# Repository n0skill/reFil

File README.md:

# reFil
A machine that makes filament suitable for 3D printers out of normally unrecycled plastic parts such as HDPE from bottle caps, failed prints etc.

# Folders
* schematics - All of the schematics made with KiCAD. Including the gerber files, kicad files (schematic, netlist, pcb, etc.)
* src - The source code running on the arduino nano (arduino/C/AVR ASM)
* mechanics - mechanical parts

# Material
The following material is needed for the whole project.

## Mechanical parts
The machine is made of lathed aluminium and brass.
All the plans will be available in the "mechanical" folder. Including 3D models, plans and specs

## Electrical parts
The controller board consists of an arduino nano and a custom board. Using a 24V power supply, a LM7805 regulator is used to drop down the voltage to a usable 5V signal to drive the logic. Since the drop is quite significant and the LM7805 is a simple linear regulator, a decent amount of heat will be produced. This can compromise the functionality of the circuit, so a heat sink has to be appended to it in order to better disipate the heat.

The board will be used to: 
1) display the current temperature
2) drive the motor
3) drive the heating element

### Temperature sensor
The temperature sensor consists of a PT1000 RTD as part of a voltage divider circuit. The conversion from voltage to temperature can be made by either: looking up a table, or using a formula.

Once the temperature is known, the arduino uses BCD encoding to controll the CD4543BE 7 segment display driver, which displays the temperature.

### Motor driver
The motor is a E192.24.246 Micromotors brushed DC thing. It has a 1:246 gearbox that allows it to move things with a high torque (at the expense of a lower rate of rotation. But we don't care about that)

It is using the 24V from the barrel jack and is toggled using a SRD-05VDC-SL-C relay from SONGLE industries.

### Heating element

The heating element is a simple nichrome wire that is also toggled with a relay on the 24V power line.

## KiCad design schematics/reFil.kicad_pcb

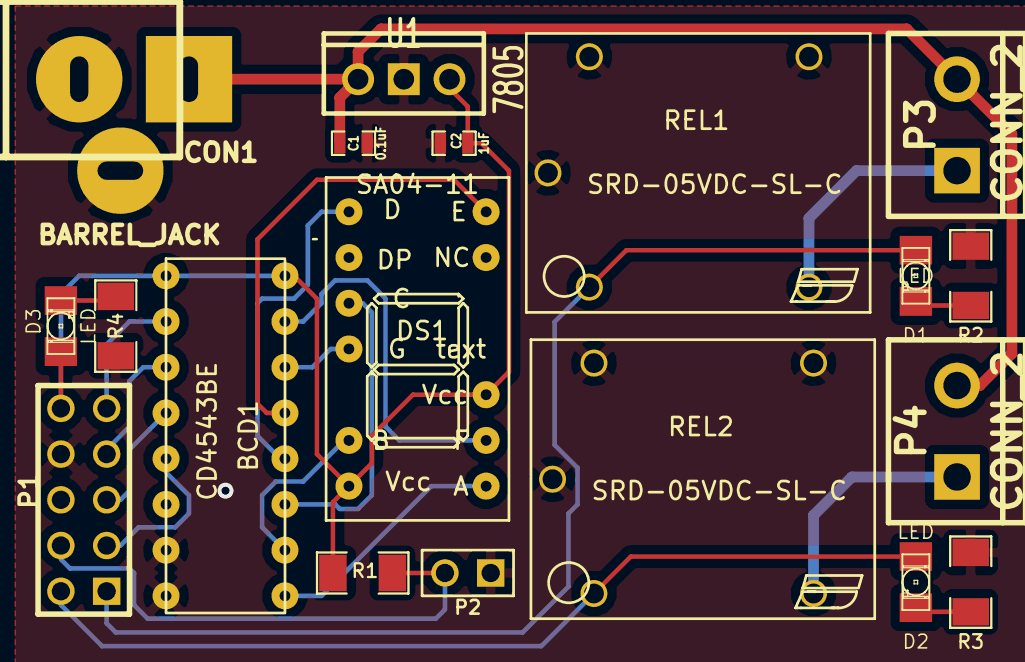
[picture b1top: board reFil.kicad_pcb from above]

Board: 2 copper layers, 19 parts (0 on the bottom side), 22 nets.

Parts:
BCD1: CD4543BE
C1: 0.1uF; SM0603_Capa
C2: 1uF; SM0603_Capa
CON1: BARREL_JACK; JACK_ALIM
D1, D2, D3: LED; LED-1206
DS1: SA04-11; SA03-11
P1: CONN_5X2; PIN_ARRAY_5x2
P2: CONN_2; PIN_ARRAY_2X1
P3, P4: CONN_2; bornier2
R1: 10K; SM1206
R2, R3, R4: 18k; SM1206
REL1, REL2: SRD-05VDC-SL-C
U1: 7805; LM78XXV

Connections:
+5V: BCD1.1, BCD1.16, C2.1, D3.1, DS1.3, DS1.14, P1.10, R1.1, U1.VO
+24V: C1.1, CON1.1, P3.2, P4.2, U1.VI
A: BCD1.5, P1.3
B: BCD1.3, P1.7
C: BCD1.2, P1.9
D: BCD1.4, P1.5
GND: BCD1.7, BCD1.8, C1.2, C2.2, CON1.2, CON1.3, P1.8, P2.1, R2.2, R3.2, R4.2, REL1.3, REL1.4, REL1.5, REL2.3, REL2.4, REL2.5, U1.GND
HEAT: D1.1, P1.1, REL1.1
MOTOR: D2.1, P1.2, REL2.1
unnamed: D1.2, R2.1
unnamed: P4.1, REL2.2
unnamed: P3.1, REL1.2
unnamed: BCD1.14, DS1.11
unnamed: BCD1.15, DS1.2
unnamed: BCD1.13, DS1.7
unnamed: BCD1.12, DS1.8
unnamed: BCD1.11, DS1.10
unnamed: BCD1.10, DS1.13
unnamed: BCD1.9, DS1.1
unnamed: D2.2, R3.1
unnamed: D3.2, R4.1
TEMP: P1.4, P2.2, R1.2

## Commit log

2016-06-03 Fixing issues. Adding 3d view of the board
2016-06-03 Create README.md
    Adding description
2016-06-08 Better layout
2016-06-08 Add exported and gerber files
2016-06-09 Electrolytic caps -> ceramic SMD caps. Also debugging LEDS.
2016-06-27 Fix relay footprint pins diameter. Rearrange layout of board for easier mounting.
2016-06-27 Added sample arduino code
2016-06-27 Expanded the README.md a bit
2016-06-27 fix headers in readme
2016-07-01 Starting new layout. Better bornier placement.
2016-07-01 Arduino code rework.
2016-07-01 Add corrected temp.ino file
2016-07-01 Add 3D modeling of the motor and the shaft connector
2016-07-04 New board layout and gerber export
    The 24V connectors (P3, P4) face the opposite side of the barrel jack.
    The power LED is now between the barrel jack and the P1 connector
    The thermistance connector is now below the temperature display
2016-07-04 Fix gerber export
    Add the schematics/export folder to the repo
